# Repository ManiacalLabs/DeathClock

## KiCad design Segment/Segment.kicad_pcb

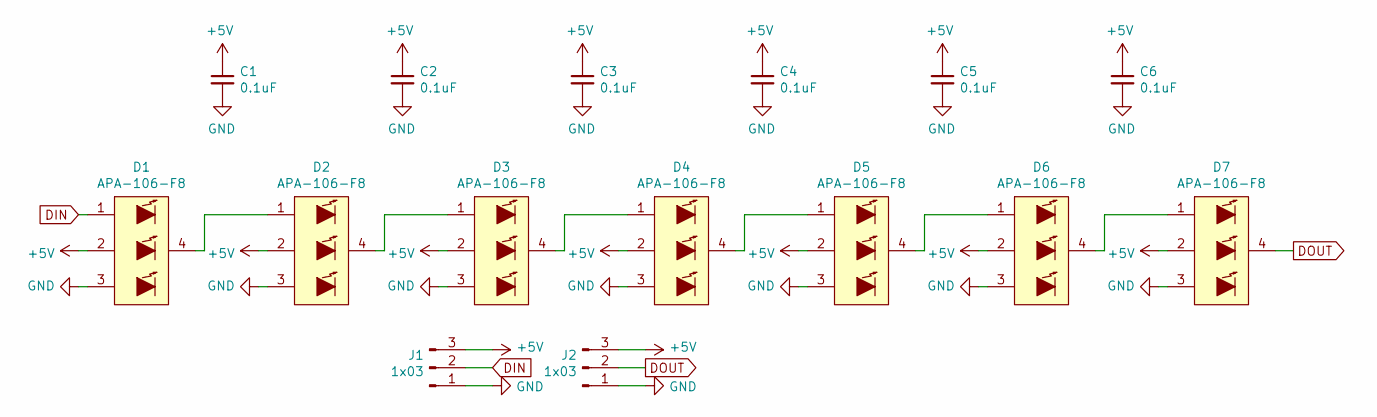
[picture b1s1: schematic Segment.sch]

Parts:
C1, C2, C3, C4, C5, C6: 0.1uF; cnp_3mm_disc
D1, D2, D3, D4, D5, D6, D7: APA-106-F8
J1, J2: 1x03; 7SegmentCorner

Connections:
+5V: C1.1, C2.1, C3.1, C4.1, C5.1, C6.1, D1.2 (VDD), D2.2 (VDD), D3.2 (VDD), D4.2 (VDD), D5.2 (VDD), D6.2 (VDD), D7.2 (VDD), J1.3, J2.3
DIN: D1.1 (DIN), J1.2
DOUT: D7.4 (DOUT), J2.2
GND: C1.2, C2.2, C3.2, C4.2, C5.2, C6.2, D1.3 (GND), D2.3 (GND), D3.3 (GND), D4.3 (GND), D5.3 (GND), D6.3 (GND), D7.3 (GND), J1.1, J2.1
unnamed: D1.4 (DOUT), D2.1 (DIN)
unnamed: D2.4 (DOUT), D3.1 (DIN)
unnamed: D3.4 (DOUT), D4.1 (DIN)
unnamed: D4.4 (DOUT), D5.1 (DIN)
unnamed: D5.4 (DOUT), D6.1 (DIN)
unnamed: D6.4 (DOUT), D7.1 (DIN)

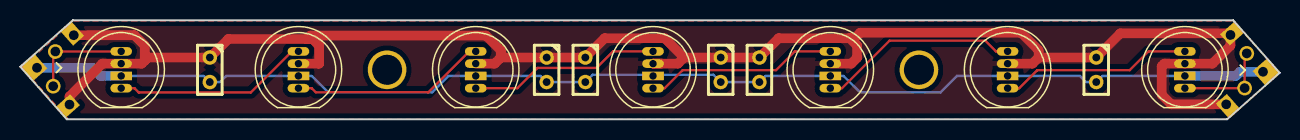
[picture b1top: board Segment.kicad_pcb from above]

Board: 2 copper layers, 130.2 x 10.2 mm, 15 parts (0 on the bottom side), 10 nets.

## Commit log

2019-03-02 Adding main segment PCB
2019-03-02 Added text and logos. Ordered version
2019-03-26 Fixing footprints
2019-04-08 Fix shorts
2019-04-15 Adding single digit test
2019-04-16 Updating single digit animation
2019-04-18 Adding new animations
2019-04-23 Adding F360 for segment
2019-04-23 decrease brightness
2019-05-14 Refilling zones
